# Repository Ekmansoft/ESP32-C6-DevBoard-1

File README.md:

# ESP32-C6-DevBoard-1
Open source ESP32-C6 Devboard 

Intended to be useful for others when it is done.

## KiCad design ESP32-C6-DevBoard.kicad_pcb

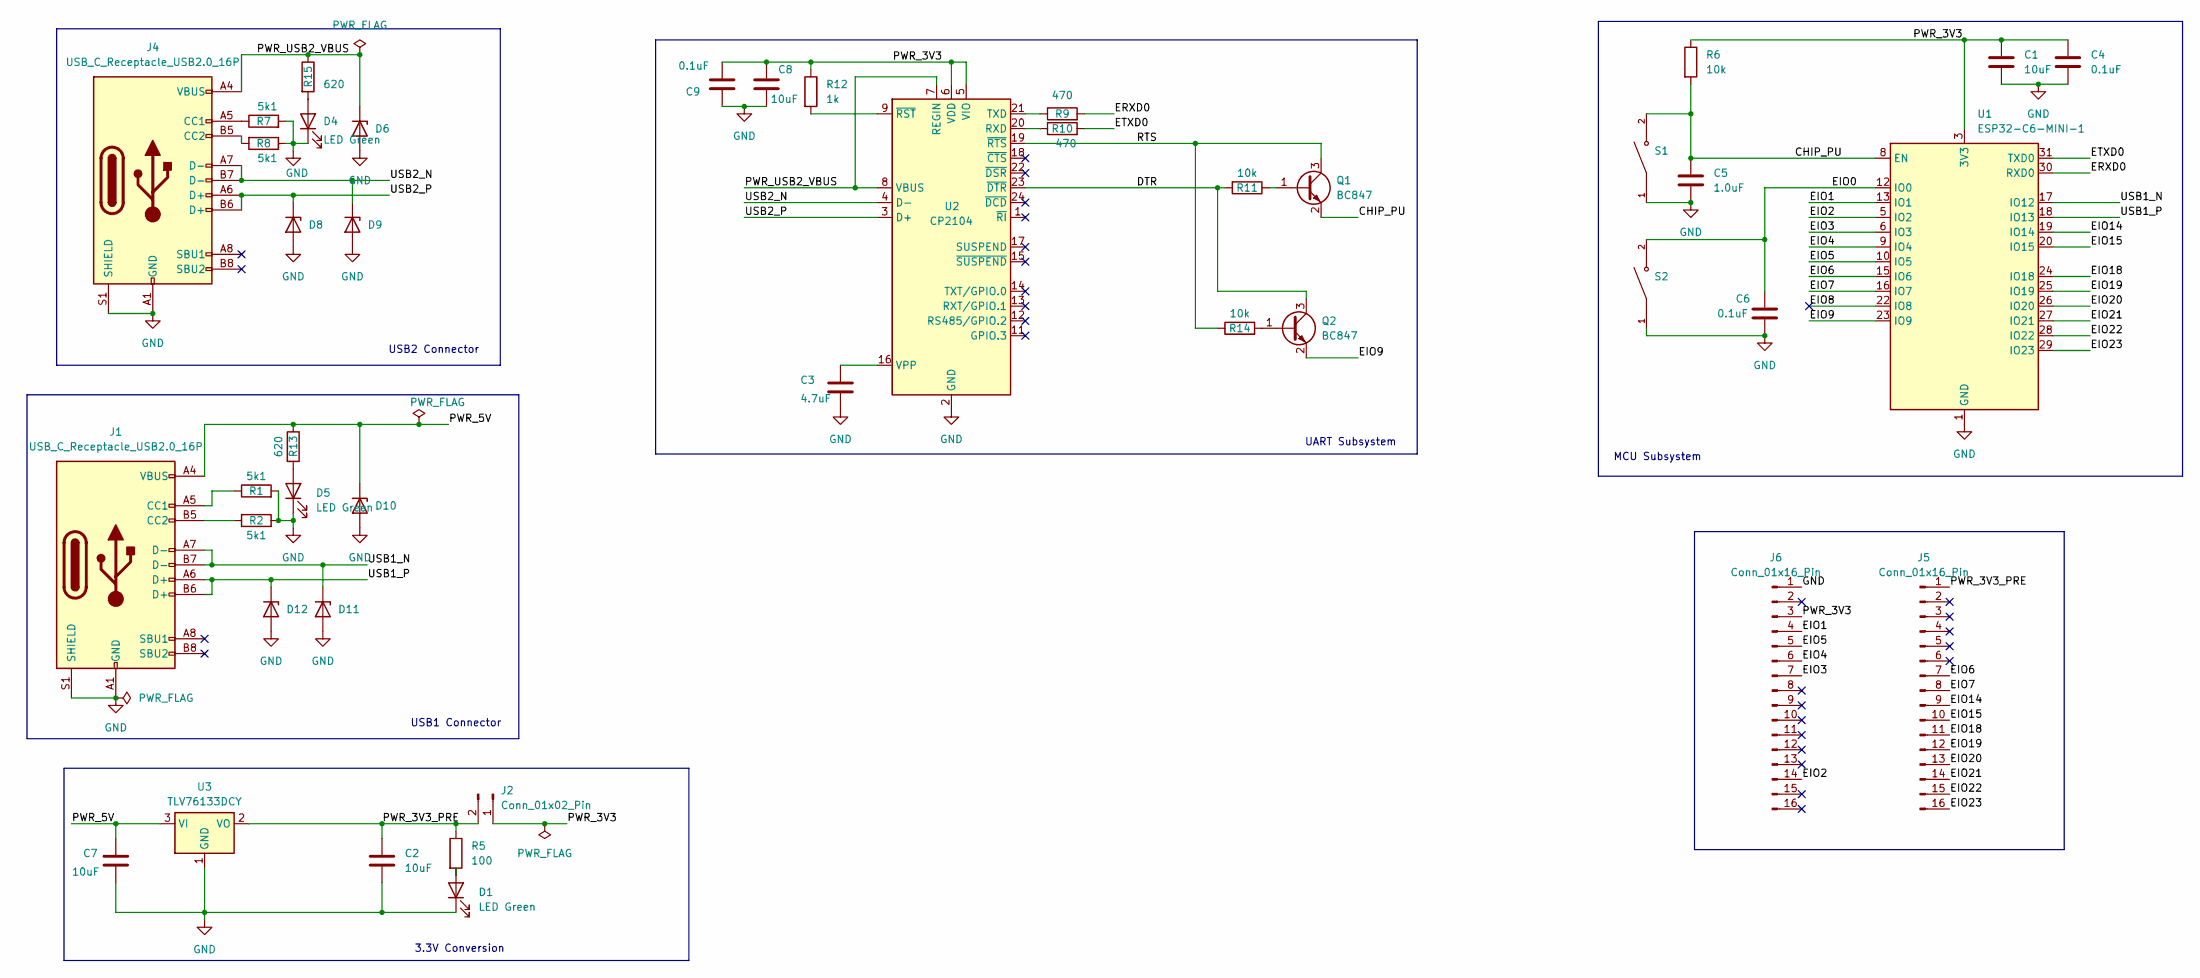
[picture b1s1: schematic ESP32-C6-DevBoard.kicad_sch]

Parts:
C1, C2, C7, C8: 10uF; C_0603_1608Metric; Part_No Samsung Electro-Mechanics CL10A106MA8NR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; LCSC C96446
C3: 4.7uF; C_0603_1608Metric; Part_No Samsung Electro-Mechanics CL10A475KO8NN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; LCSC C19666
C4, C6, C9: 0.1uF; C_0603_1608Metric; Part_No FH (Guangdong Fenghua Advanced Tech) 06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; LCSC C1590
C5: 1.0uF; C_0603_1608Metric; Part_No Samsung Electro-Mechanics CL10A105KB8NN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; LCSC C1592
D1: LED Green; LED_0603_1608Metric; Part_No Lite-On LTW-C191TS5; LCSC C12065
D4: LED Green; LED_0603_1608Metric; Part_No Lite-On LTST-C193TBKT-5A; LCSC C12065
D5: LED Green; LED_0603_1608Metric; Part_No Lite-On LTST-C193TGKT-5A; LCSC C12065
D6, D8, D9, D10, D11, D12: SD05_SOD323; D_SOD-882; Part_No MDD(Microdiode Semiconductor) SD05; LCSC C502527
J1, J4: USB_C_Receptacle_USB2.0_16P; USB_C_Receptacle_HRO_TYPE-C-31-M-12; Part_No SHOU HAN TYPE-C 16PIN 2MD(073); LCSC C2765186
J2: Conn_01x02_Pin; PinHeader_1x02_P2.54mm_Vertical; Part_No Ckmtw(Shenzhen Cankemeng) B-2100S02P-A1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; LCSC C706874
J5, J6: Conn_01x16_Pin; PinHeader_1x16_P2.54mm_Vertical; Part_No HanElectricity 2541WV-16P; LCSC C725948
Q1, Q2: BC847; SOT-23; Part_No Nexperia BC847B,215; LCSC C57668
R1, R2, R7, R8: 5k1; R_0603_1608Metric; Part_No UNI-ROYAL(Uniroyal Elec) 0603WAF5101T5E; LCSC C23186
R5: 100; R_0603_1608Metric; Part_No UNI-ROYAL(Uniroyal Elec) 0603WAF510JT5E; LCSC C22775
R6, R11, R14: 10k; R_0603_1608Metric; Part_No UNI-ROYAL(Uniroyal Elec) 0603WAF1002T5E; LCSC C25804
R9, R10: 470; R_0603_1608Metric; Part_No UNI-ROYAL(Uniroyal Elec) 0603WAF510JT5E; LCSC C23179
R12: 1k; R_0603_1608Metric; Part_No UNI-ROYAL(Uniroyal Elec) 0603WAF4700T5E; LCSC C21190
R13, R15: 620; R_0603_1608Metric; Part_No UNI-ROYAL(Uniroyal Elec) 0603WAF510JT5E; LCSC C23220
S1, S2: TS-1088-AR02016; SW_TS-1088-AR02016; PARTREV N/A; LCSC C720477
U1: ESP32-C6-MINI-1; Part_No Espressif Systems ESP32-C6-MINI-1-N4; LCSC C5736265
U2: CP2104; QFN-24-1EP_4x4mm_P0.5mm_EP2.6x2.6mm; Part_No SKYWORKS/SILICON LABS CP2104-F03-GMR; LCSC C47742
U3: TLV76133DCY; SOT-223-3_TabPin2; LCSC C7527500

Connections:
/CHIP_PU: C5.1, Q1.2 (E), R6.2, S1.2, U1.8 (EN)
/DTR: Q2.3 (C), R11.2, U2.23 (~DTR)
/EIO0: C6.1, S2.2, U1.12 (IO0)
/EIO1: J6.4, U1.13 (IO1)
/EIO2: J6.14, U1.5 (IO2)
/EIO3: J6.7, U1.6 (IO3)
/EIO4: J6.6, U1.9 (IO4)
/EIO5: J6.5, U1.10 (IO5)
/EIO6: J5.7, U1.15 (IO6)
/EIO7: J5.8, U1.16 (IO7)
/EIO8: U1.22 (IO8)
/EIO9: Q2.2 (E), U1.23 (IO9)
/EIO14: J5.9, U1.19 (IO14)
/EIO15: J5.10, U1.20 (IO15)
/EIO18: J5.11, U1.24 (IO18)
/EIO19: J5.12, U1.25 (IO19)
/EIO20: J5.13, U1.26 (IO20)
/EIO21: J5.14, U1.27 (IO21)
/EIO22: J5.15, U1.28 (IO22)
/EIO23: J5.16, U1.29 (IO23)
/ERXD0: R9.2, U1.30 (RXD0)
/ETXD0: R10.2, U1.31 (TXD0)
/PWR_3V3: C1.1, C4.1, C8.1, C9.1, J2.1, J6.3, R6.1, R12.1, U1.3 (3V3), U2.5 (VIO), U2.6 (VDD)
/PWR_3V3_PRE: C2.1, J2.2, J5.1, R5.1, U3.2 (VO)
/PWR_5V: C7.1, D10.1 (K), J1.A4 (VBUS), J1.A9 (VBUS), J1.B4 (VBUS), J1.B9 (VBUS), R13.1, U3.3 (VI)
/PWR_USB2_VBUS: D6.1 (K), J4.A4 (VBUS), J4.A9 (VBUS), J4.B4 (VBUS), J4.B9 (VBUS), R15.1, U2.7 (REGIN), U2.8 (VBUS)
/RTS: Q1.3 (C), R14.1, U2.19 (~RTS)
/USB1_N: D11.1 (K), J1.A7 (D-), J1.B7 (D-), U1.17 (IO12)
/USB1_P: D12.1 (K), J1.A6 (D+), J1.B6 (D+), U1.18 (IO13)
/USB2_N: D9.1 (K), J4.A7 (D-), J4.B7 (D-), U2.4 (D-)
/USB2_P: D8.1 (K), J4.A6 (D+), J4.B6 (D+), U2.3 (D+)
GND: C1.2, C2.2, C3.2, C4.2, C5.2, C6.2, C7.2, C8.2, C9.2, D1.1 (K), D4.1 (K), D5.1 (K), D6.2 (A), D8.2 (A), D9.2 (A), D10.2 (A), D11.2 (A), D12.2 (A), J1.A1 (GND), J1.A12 (GND), J1.B1 (GND), J1.B12 (GND), J1.S1 (SHIELD), J4.A1 (GND), J4.A12 (GND), J4.B1 (GND), J4.B12 (GND), J4.S1 (SHIELD), J6.1, R1.2, R2.2, R7.2, R8.1, S1.1, S2.1, U1.1 (GND), U1.2 (GND), U1.11 (GND), U1.14 (GND), U1.36 (GND), U1.37 (GND), U1.38 (GND), U1.39 (GND), U1.40 (GND), U1.41 (GND), U1.42 (GND), U1.43 (GND), U1.44 (GND), U1.45 (GND), U1.46 (GND), U1.47 (GND), U1.48 (GND), U1.49 (GND), U1.50 (GND), U1.51 (GND), U1.52 (GND), U1.53 (GND), U2.2 (GND), U2.25 (GND), U3.1 (GND)
unnamed: D1.2 (A), R5.2
unnamed: D4.2 (A), R15.2
unnamed: D5.2 (A), R13.2
unnamed: J1.A5 (CC1), R1.1
unnamed: J1.B5 (CC2), R2.1
unnamed: J4.A5 (CC1), R7.1
unnamed: J4.B5 (CC2), R8.2
unnamed: Q1.1 (B), R11.1
unnamed: Q2.1 (B), R14.2
unnamed: R10.1, U2.20 (RXD)
unnamed: R9.1, U2.21 (TXD)
unnamed: C3.1, U2.16 (VPP)
unnamed: R12.2, U2.9 (~RST)

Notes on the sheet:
MCU Subsystem
USB2 Connector
USB1 Connector
UART Subsystem
3.3V Conversion

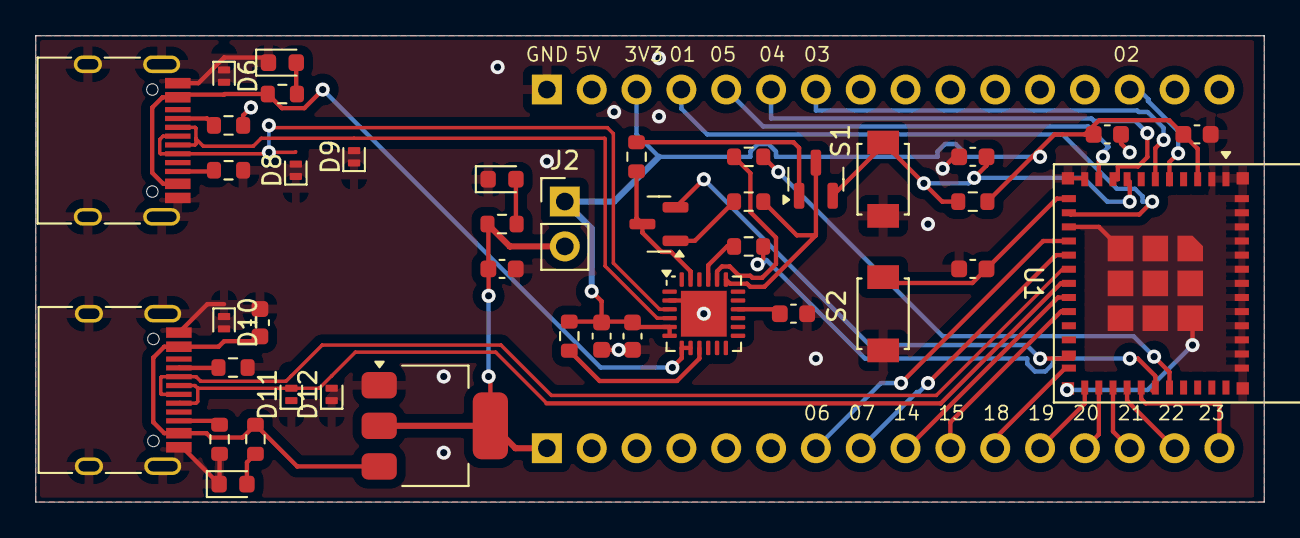
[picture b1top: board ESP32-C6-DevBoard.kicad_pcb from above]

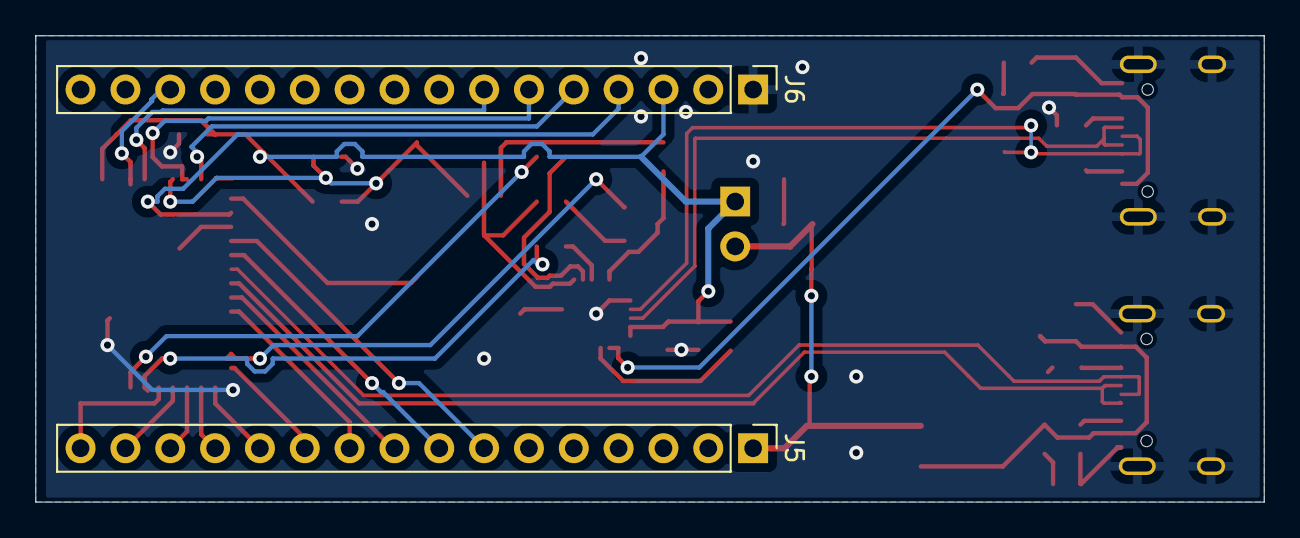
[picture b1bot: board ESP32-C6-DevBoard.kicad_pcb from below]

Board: 2 copper layers, 69.6 x 26.4 mm, 43 parts (2 on the bottom side), 44 nets.

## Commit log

2025-05-17 First test version
2025-05-17 Fixed missing file
2025-05-31 First version done without autorouter.
2025-06-01 Updated silk screen and corrected component error
2025-06-01 Updated board size and 3D models
2025-06-02 Move vias placed on pads
2025-06-03 Updated BOM
2025-06-03 Updated BOM with LCSC part number
2025-06-03 Added ods version of BOM
2025-06-06 Updated BOM using Buoni kicad-jlcpcb-tools
2025-06-22 Updated settings
2025-07-14 Changed to better USB-C connector footprint. Reduced size Changed to 1A 3.3V converter
2025-07-19 Further improvements
2025-08-27 Change to unidirectional diodes (as that is what I actuallt ordered)
